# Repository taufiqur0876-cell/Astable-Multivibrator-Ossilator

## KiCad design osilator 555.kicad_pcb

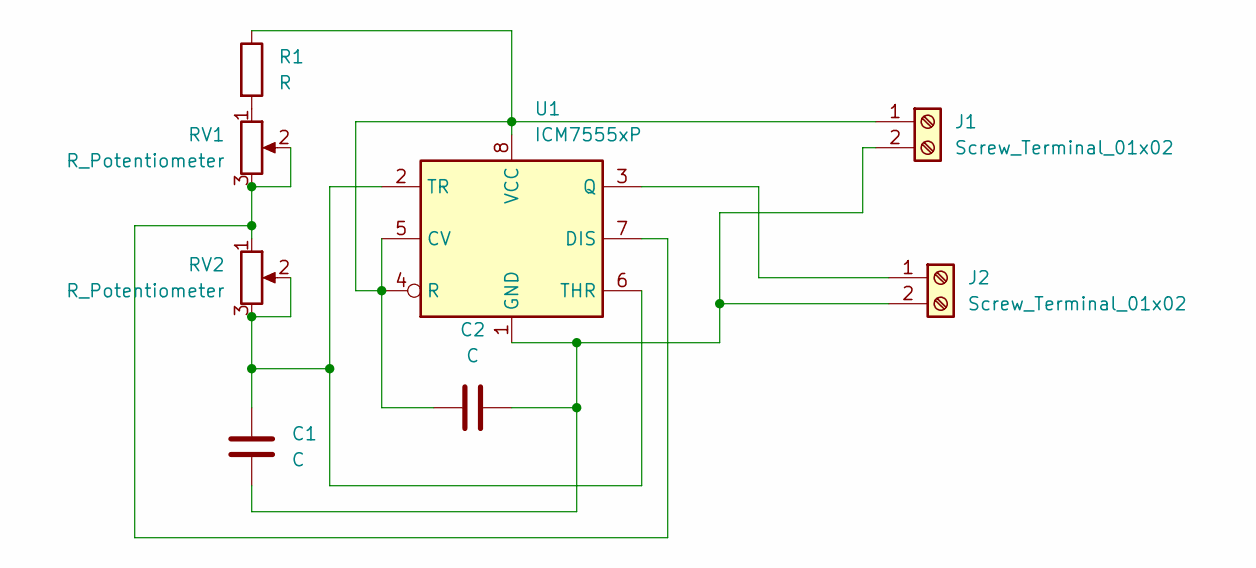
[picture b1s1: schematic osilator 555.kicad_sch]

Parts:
C1, C2: C; C_Radial_D10.0mm_H12.5mm_P5.00mm
J1, J2: Screw_Terminal_01x02; TerminalBlock_bornier-2_P5.08mm
R1: R; R_Axial_DIN0411_L9.9mm_D3.6mm_P12.70mm_Horizontal
RV1, RV2: R_Potentiometer; Potentiometer_Piher_PC-16_Single_Horizontal
U1: ICM7555xP; DIP-8_W7.62mm

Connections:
unnamed: C2.1, J1.1, R1.1, U1.4 (R), U1.5 (CV), U1.8 (VCC)
unnamed: C1.2, C2.2, J1.2, J2.2, U1.1 (GND)
unnamed: J2.1, U1.3 (Q)
unnamed: R1.2, RV1.1
unnamed: RV1.2, RV1.3, RV2.1, U1.7 (DIS)
unnamed: C1.1, RV2.2, RV2.3, U1.2 (TR), U1.6 (THR)

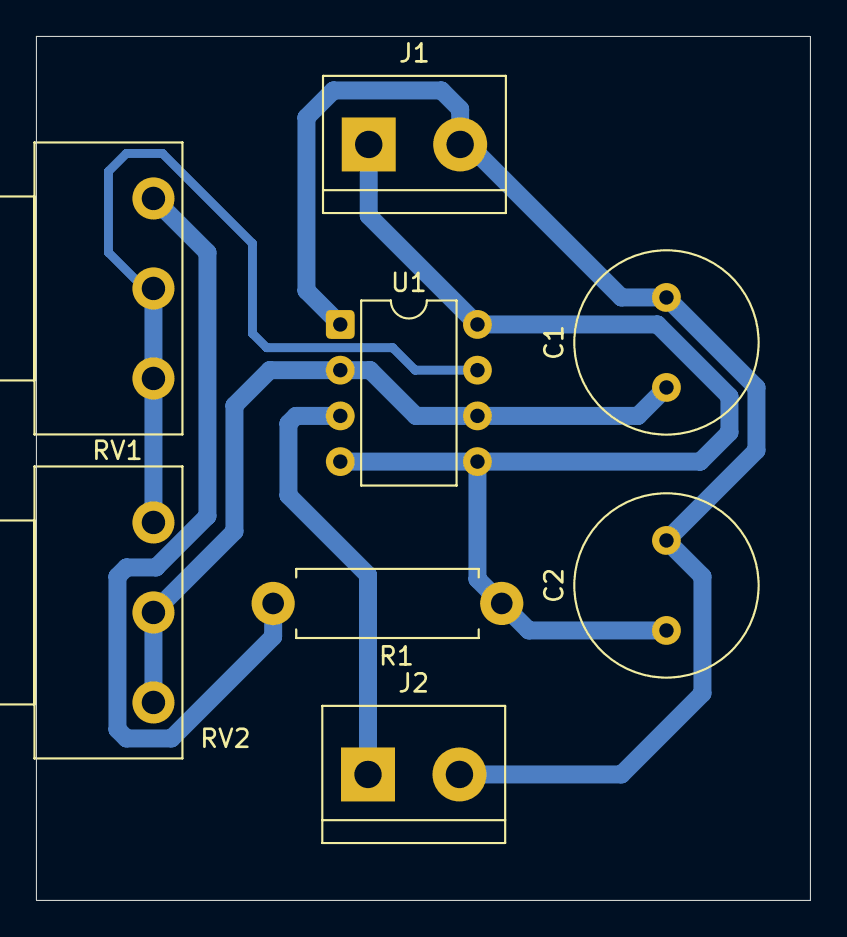
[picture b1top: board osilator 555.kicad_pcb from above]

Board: 2 copper layers, 43.0 x 48.0 mm, 8 parts (0 on the bottom side), 6 nets.
